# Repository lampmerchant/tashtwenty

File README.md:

# TashTwenty

## Elevator Pitch

It's a DCD (the interface used by the Hard Disk 20 to plug in through the disk port) interface, contained entirely within a PIC16F1825 (14 pins, ~$1.84) or PIC16F1704 (14 pins, ~$1.39) microcontroller. It bit-bangs the low-level IWM protocol using the read/write and phase lines on the "DB"-19 disk port, no programmable logic devices of any kind required.

It interfaces to an MMC or compatible card and can emulate up to four DCD devices.  It also has an enable output which can be used to chain more DCD devices (though ROMs only support a maximum of four) and a floppy disk drive.

(Despite the name, there is nothing limiting it to 20 megabytes.)

## Project Status

Functional, though not rigorously tested.

## Caveats

Due to the dearth of documentation on the DCD protocol, the protocol only implements the commands whose formats are known, namely read, write, and device identification.  Responses to other commands are faked.  Fortunately, this seems to be enough for the device to function properly, including formatting.

The disk drive interface relies on use of the phase lines to read and write one-bit registers.  Because the PIC16F1825 firmware mimics the register set in code instead of programmable logic, it has a response time that is, in the worst case, approximately one microsecond.  This may interfere with the ability of faster Macs to detect it, though it is not known to do so at this point.  The PIC16F1704 firmware mimics the register set in logic and responds in effect instantly.

Certain Macs may have a limitation imposed by their ROM on the number of DCDs they support.  See [this link](https://github.com/lampmerchant/tashnotes/blob/main/macintosh/floppy/dcd/dcd.md) for details.

## PCBs and Products

* TashTwenty Tiny by [demik](https://github.com/demik)
   * [Files](https://github.com/lampmerchant/tashtwenty/tree/main/pcb/TashTwenty%20Tiny)
   * See latest release in this repository for gerbers
   * [Buy](https://ko-fi.com/s/2bfee029f5) from [CayMac Vintage](https://ko-fi.com/caymacvintage/shop)
   * Buy [PCBs](https://ko-fi.com/s/01a52bed98), [case panels](https://ko-fi.com/s/50199947e3), and [programmed PICs](https://ko-fi.com/s/2b28fb5562) from [Tashtari](https://ko-fi.com/tashtari/shop)
* TashTwenty Internal by [cheesestraws](https://github.com/cheesestraws)
   * [Files](https://github.com/lampmerchant/tashtwenty/tree/main/pcb/Internal)
   * See latest release in this repository for gerbers
* TashTwenty Rev 3 by [Tashtari](https://github.com/lampmerchant)
   * [Files](https://github.com/lampmerchant/tashtwenty/blob/main/pcb/tashtari-tashtwenty.brd)
   * See latest release in this repository for gerbers
* TashTwenty Budget Version by [CayMac Vintage](https://ko-fi.com/caymacvintage/shop)
   * [Buy](https://ko-fi.com/s/77f53b293e)
* TashTwenty Mega by [warmech](https://68kmla.org/bb/index.php?members/warmech.2497/)
   * Pending release
* TashTwenty Vertical by [hideehoo](https://68kmla.org/bb/index.php?members/hideehoo.4611/)
   * Pending release

## Technical Details

### Building Firmware

Building the firmware requires Microchip MPASM, which is included with their development environment, MPLAB.  Note that you **must** use MPLAB X version 5.35 or earlier or MPLAB 8 as later versions of MPLAB X have removed MPASM.

The firmware can also be built using gpasm, an MPASM-compatible assembler that is part of the [gputils](https://gputils.sourceforge.io/) project.  Please note, however, that the release builds are built using MPASM and compatibility with gpasm is not tested.

### MMC Card Format

The MMC card must have an MBR (Master Boot Record) aka DOS-type partition table with up to four primary partitions of type 0xAF (HFS).  Extended partitions are not supported.

#### Custom Icons

In the PIC16F1704 firmware, custom icons are supported using other values besides 0xAF for the partition type byte.  Other partition types besides 0xAF must be the number of a sector (for example, a partition of type 0x01 would point to the second sector) on the card formatted as follows:

* Bytes 0-255 must be the word "ICON" repeated 64 times.
* Bytes 256-383 must be a 32x32 icon, one bit per pixel, with '1' bits denoting black and '0' bits denoting white.
* Bytes 384-511 must be a 32x32 icon mask, one bit per pixel, with '1' bits denoting opaque and '0' bits denoting transparent.

If the sector is not in this format, the partition will be ignored, in order to safely support cards with non-HFS partitions.  Partitions of type 0xAF will always use the built-in icon and the hundred-seventy-sixth sector will not be checked for the format described above.

### DCD (Directly Connected Disks) Protocol

See [this link](https://github.com/lampmerchant/tashnotes/tree/main/macintosh/floppy/dcd) for details.

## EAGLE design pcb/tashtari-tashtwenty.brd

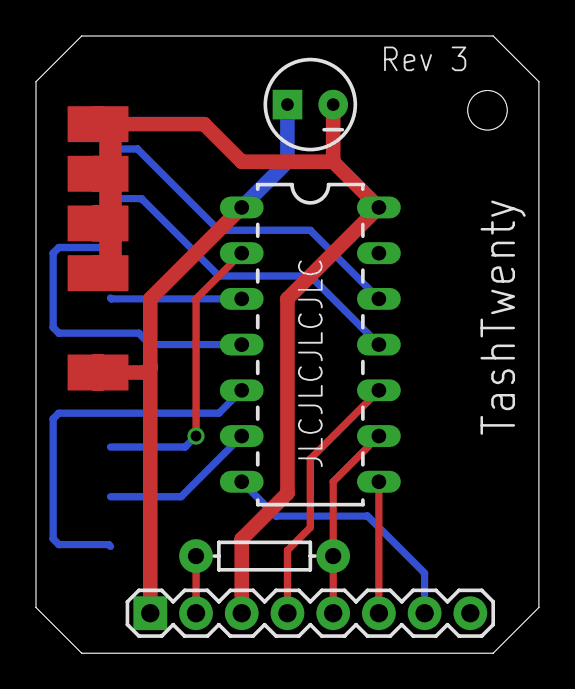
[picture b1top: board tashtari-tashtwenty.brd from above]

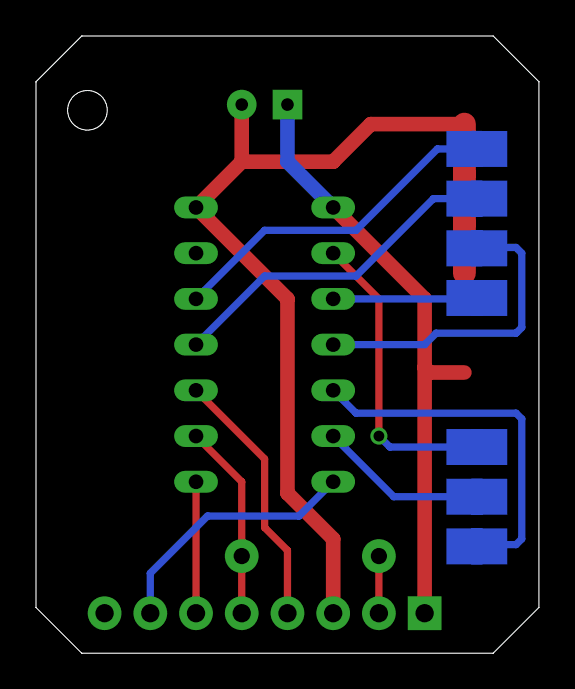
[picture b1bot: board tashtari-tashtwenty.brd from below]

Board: 2 copper layers, 27.9 x 34.3 mm, 28 parts (14 on the bottom side), 14 nets.

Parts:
E$3, E$4, E$8, E$9, E$10, E$11, E$12, E$13, E$14, E$15, E$18, E$19, E$21, E$22, E$24, E$25, E$27, E$28, E$31, E$32, E$33, E$34, E$35, E$36: TP20SQ
E$37: DIL14
E$38: 1X08
E$39: CPOL-RADIAL-10UF-25V
E$40: AXIAL-0.3

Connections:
S$1: E$14.TP, E$37.1, E$38.1, E$39.1
S$2: E$4.TP, E$9.TP, E$11.TP, E$13.TP, E$37.14, E$38.3, E$39.2
S$3: E$37.7, E$38.7
S$4: E$37.8, E$38.6
S$5: E$37.10, E$38.4
S$6: E$37.9, E$38.5, E$40.P$2
S$7: E$32.TP, E$37.5
S$8: E$34.TP, E$37.6
S$9: E$35.TP, E$37.2
S$10: E$28.TP, E$37.3
S$11: E$25.TP, E$37.4
S$12: E$22.TP, E$37.11
S$13: E$19.TP, E$37.12
S$14: E$38.2, E$40.P$1

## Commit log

2021-11-03 20211103
2021-11-06 20211106
2021-11-14 20211114
2021-11-20 20211120
2021-11-23 20211122
2021-11-26 20211126
2021-11-26 add board rev 1
2021-11-26 update README to mention use of MBR
2021-11-28 20211128
2022-03-17 initial relase of the TashTwentt Tiny PCB: a dual PCB THT implementation of TashTwenty
2022-03-18 added TTT adapter board
2022-03-18 added small readme and BOM
2022-03-19 added mouser basket link
2022-03-19 update README.md with compatibility information
2022-03-20 added librairy for DB19
2022-03-20 added GitHub, 68kmla URLs and revisions to source files
2022-03-21 added info about BOMs, mouser basket, etc…
2022-03-21 added info for IDC-20 cable
2022-03-24 Updated mouser basket link
2022-04-01 fixed typo (J1 -> J3)
2022-04-01 Basket update + more J3 documentation
2022-04-10 update README with new info about compatibility
2022-04-14 update README.md with new info about number of DCDs
2022-04-21 20220421
2022-04-22 update README.md with particulars of PIC16F1704 firmware
2022-04-24 20220424
2022-05-01 1825/IIcx compatibility demonstrated
2022-05-01 add system software compatibility table
2022-05-10 added PCB Front Panel
2022-05-10 refreshed Mouser Basket
2022-05-10 added Ribbon Cable P/N
2022-05-11 added digikey basket
2022-05-17 added back panel PCB
2022-05-20 added missing TTT_BP.kicad_pcb
2022-05-21 PCB board rev 1.1: fixed R2 silkscreen
2022-06-04 20220604
2022-06-06 Switched PIC P/N to PIC16F1704
2022-06-06 updates mouser basket to 20220606
2022-06-06 PCB board rev 1.2: fix LED positions
2022-06-07 Rev 1.1 Front Panel: align LED and SD holes
2022-06-11 20220611
2022-06-22 20220621
2022-10-14 translate DCD document from MacDex
2022-10-14 missed translating a header from wiki markup
2022-12-01 note removal of MPASM from MPLAB X
2023-02-21 move DCD documentation to tashnotes
2024-02-28 Internal
2024-02-28 remove gerbers (they go in release)
2024-02-28 add list of PCBs/products to README
2024-04-04 fix Tashtari link
2024-05-28 add FUNDING.yml with ko-fi
2026-05-30 mention gputils as potential build tool

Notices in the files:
parts and their libraries:
SparkFun-Capacitors: Licensing: Creative Commons ShareAlike 4.0 International - https://creativecommons.org/licenses/by-sa/4.0
